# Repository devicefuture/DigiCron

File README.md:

# DigiCron
Software and hardware for the DigiCron smartwatch.

Want to try out the DigiCron's firmware in your browser? Just visit the [DigiCron Simulator](https://digicron.devicefuture.org/simulator)!

## Getting the code
You must clone this repo like this:

```bash
git clone --recurse-submodules https://github.com/devicefuture/digicron
```

`--recurse-submodules` must be used because this repo contains Git submodules which are used as libraries for the firmware and simulator.

## Building
Before building the firmware for the first time, you will need to install the development dependencies:

```bash
./build.sh --install-dev
```

To build the firmware and upload it to the target device over USB, run:

```bash
./build.sh --upload
```

You can also check for compilation errors without uploading by removing the `--upload` flag.

To build the firmware and the simulator, run:

```bash
./build.sh --sim
```

Then to run the simulator locally, you need to start a web server in this directory. You can run the following to start the web server at [localhost:8000](http://localhost:8000):

```bash
python3 -m http.server
```

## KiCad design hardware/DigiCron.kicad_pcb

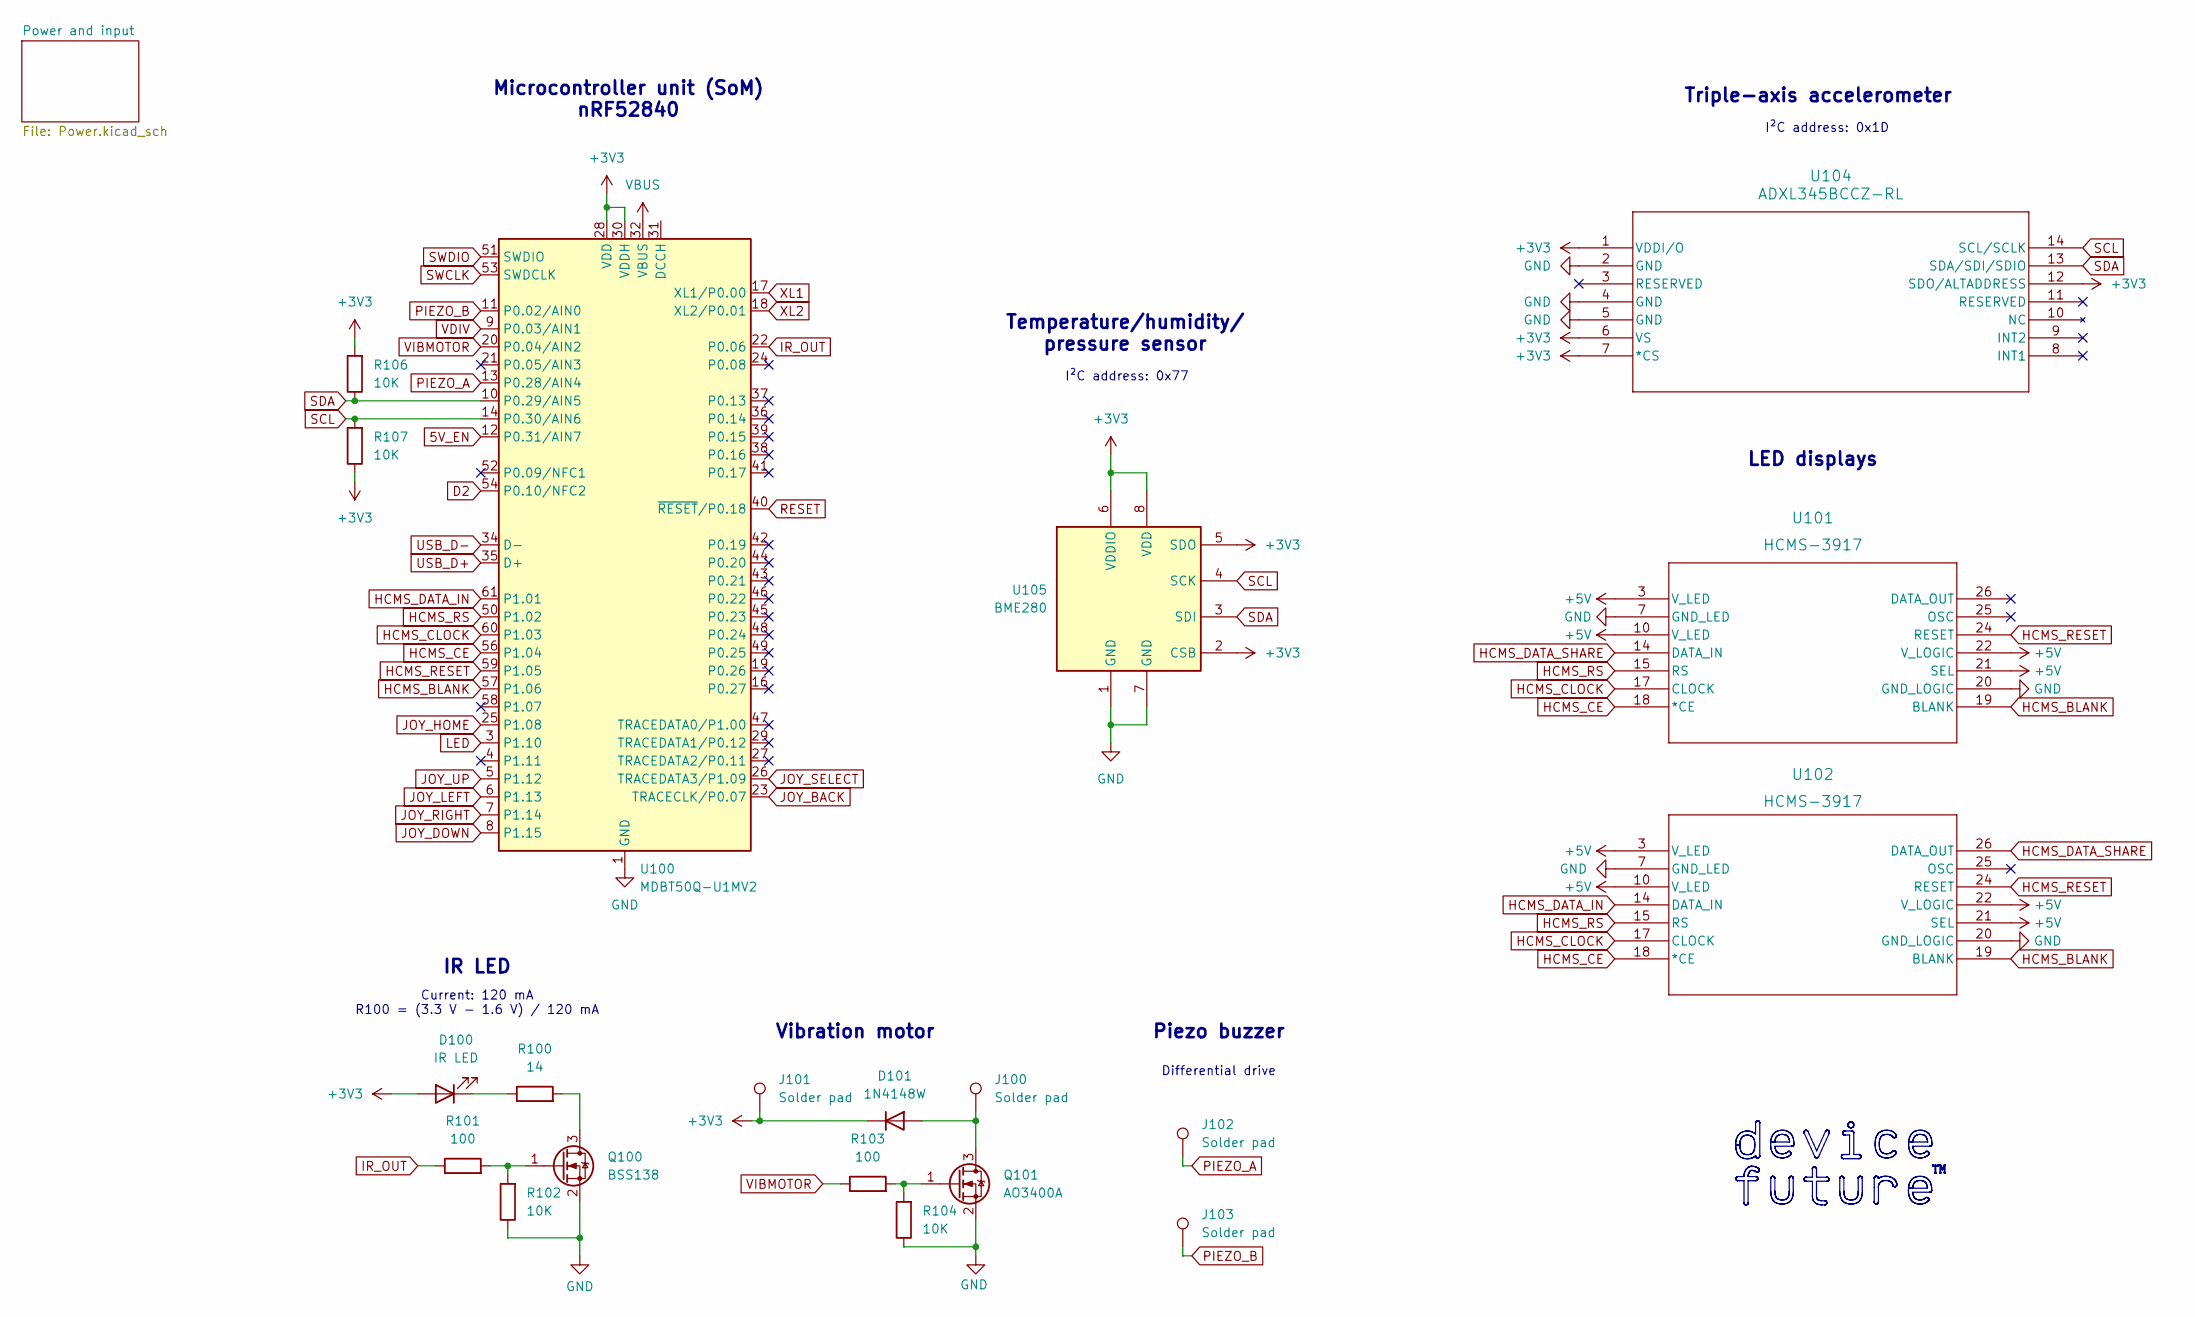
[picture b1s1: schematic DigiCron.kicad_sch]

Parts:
D100: IR LED; LED_D5.0mm_Horizontal_O1.27mm_Z3.0mm_IRBlack
D101: 1N4148W; D_SOD-123
J100, J101, J102, J103: Solder pad; SolderWirePad_1x01_SMD_1x2mm
Q100: BSS138; SOT-23
Q101: AO3400A; SOT-23
R100: 14; R_0402_1005Metric_Pad0.72x0.64mm_HandSolder
R101, R103: 100; R_0402_1005Metric_Pad0.72x0.64mm_HandSolder
R102, R104, R106, R107: 10K; R_0402_1005Metric_Pad0.72x0.64mm_HandSolder
U100: MDBT50Q-U1MV2; Raytac_MDBT50Q
U101, U102: HCMS-3917; DIP26_HCMS-290X-B_BRA
U104: ADXL345BCCZ-RL; LGA_CC-14-1_ADI
U105: BME280; Bosch_LGA-8_2.5x2.5mm_P0.65mm_ClockwisePinNumbering

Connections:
5V_EN: U100.12 (P0.31/AIN7); also elsewhere on the board
+3V3: D100.2 (A), D101.1 (K), J101.1, R106.2, R107.1, U100.28 (VDD), U100.30 (VDDH), U104.1 (VDDI/O), U104.6 (VS), U104.7 (*CS), U104.12 (SDO/ALTADDRESS), U105.2 (CSB), U105.5 (SDO), U105.6 (VDDIO), U105.8 (VDD); also elsewhere on the board
+5V: U101.3 (V_LED), U101.10 (V_LED), U101.21 (SEL), U101.22 (V_LOGIC), U102.3 (V_LED), U102.10 (V_LED), U102.21 (SEL), U102.22 (V_LOGIC); also elsewhere on the board
D2: U100.54 (P0.10/NFC2)
GND: Q100.2 (S), Q101.2 (S), R102.1, R104.1, U100.1 (GND), U100.2 (GND), U100.15 (GND), U100.33 (GND), U100.55 (GND), U101.7 (GND_LED), U101.20 (GND_LOGIC), U102.7 (GND_LED), U102.20 (GND_LOGIC), U104.2 (GND), U104.4 (GND), U104.5 (GND), U105.1 (GND), U105.7 (GND); also elsewhere on the board
HCMS_BLANK: U100.57 (P1.06), U101.19 (BLANK), U102.19 (BLANK)
HCMS_CE: U100.56 (P1.04), U101.18 (*CE), U102.18 (*CE)
HCMS_CLOCK: U100.60 (P1.03), U101.17 (CLOCK), U102.17 (CLOCK)
HCMS_DATA_IN: U100.61 (P1.01), U102.14 (DATA_IN)
HCMS_DATA_SHARE: U101.14 (DATA_IN), U102.26 (DATA_OUT)
HCMS_RESET: U100.59 (P1.05), U101.24 (RESET), U102.24 (RESET)
HCMS_RS: U100.50 (P1.02), U101.15 (RS), U102.15 (RS)
IR_OUT: R101.1, U100.22 (P0.06)
JOY_BACK: U100.23 (TRACECLK/P0.07); also elsewhere on the board
JOY_DOWN: U100.8 (P1.15); also elsewhere on the board
JOY_HOME: U100.25 (P1.08); also elsewhere on the board
JOY_LEFT: U100.6 (P1.13); also elsewhere on the board
JOY_RIGHT: U100.7 (P1.14); also elsewhere on the board
JOY_SELECT: U100.26 (TRACEDATA3/P1.09); also elsewhere on the board
JOY_UP: U100.5 (P1.12); also elsewhere on the board
LED: U100.3 (P1.10)
unnamed: D100.1 (K), R100.1
unnamed: D101.2 (A), J100.1, Q101.3 (D)
unnamed: Q100.3 (D), R100.2
unnamed: Q100.1 (G), R101.2, R102.2
unnamed: Q101.1 (G), R103.2, R104.2
PIEZO_A: J102.1, U100.13 (P0.28/AIN4)
PIEZO_B: J103.1, U100.11 (P0.02/AIN0)
RESET: U100.40 (~RESET/P0.18)
SCL: R107.2, U100.14 (P0.30/AIN6), U104.14 (SCL/SCLK), U105.4 (SCK)
SDA: R106.1, U100.10 (P0.29/AIN5), U104.13 (SDA/SDI/SDIO), U105.3 (SDI)
SWCLK: U100.53 (SWDCLK); also elsewhere on the board
SWDIO: U100.51 (SWDIO); also elsewhere on the board
USB_D+: U100.35 (D+); also elsewhere on the board
USB_D-: U100.34 (D-); also elsewhere on the board
VBUS: U100.32 (VBUS); also elsewhere on the board
VDIV: U100.9 (P0.03/AIN1); also elsewhere on the board
VIBMOTOR: R103.1, U100.20 (P0.04/AIN2)
XL1: U100.17 (XL1/P0.00); also elsewhere on the board
XL2: U100.18 (XL2/P0.01); also elsewhere on the board

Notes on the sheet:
Vibration motor
Temperature/humidity/ pressure sensor
I²C address: 0x77
LED displays
Triple-axis accelerometer
IR LED
Differential drive
I²C address: 0x1D
Piezo buzzer
Current: 120 mA R100 = (3.3 V - 1.6 V) / 120 mA
Microcontroller unit (SoM) nRF52840

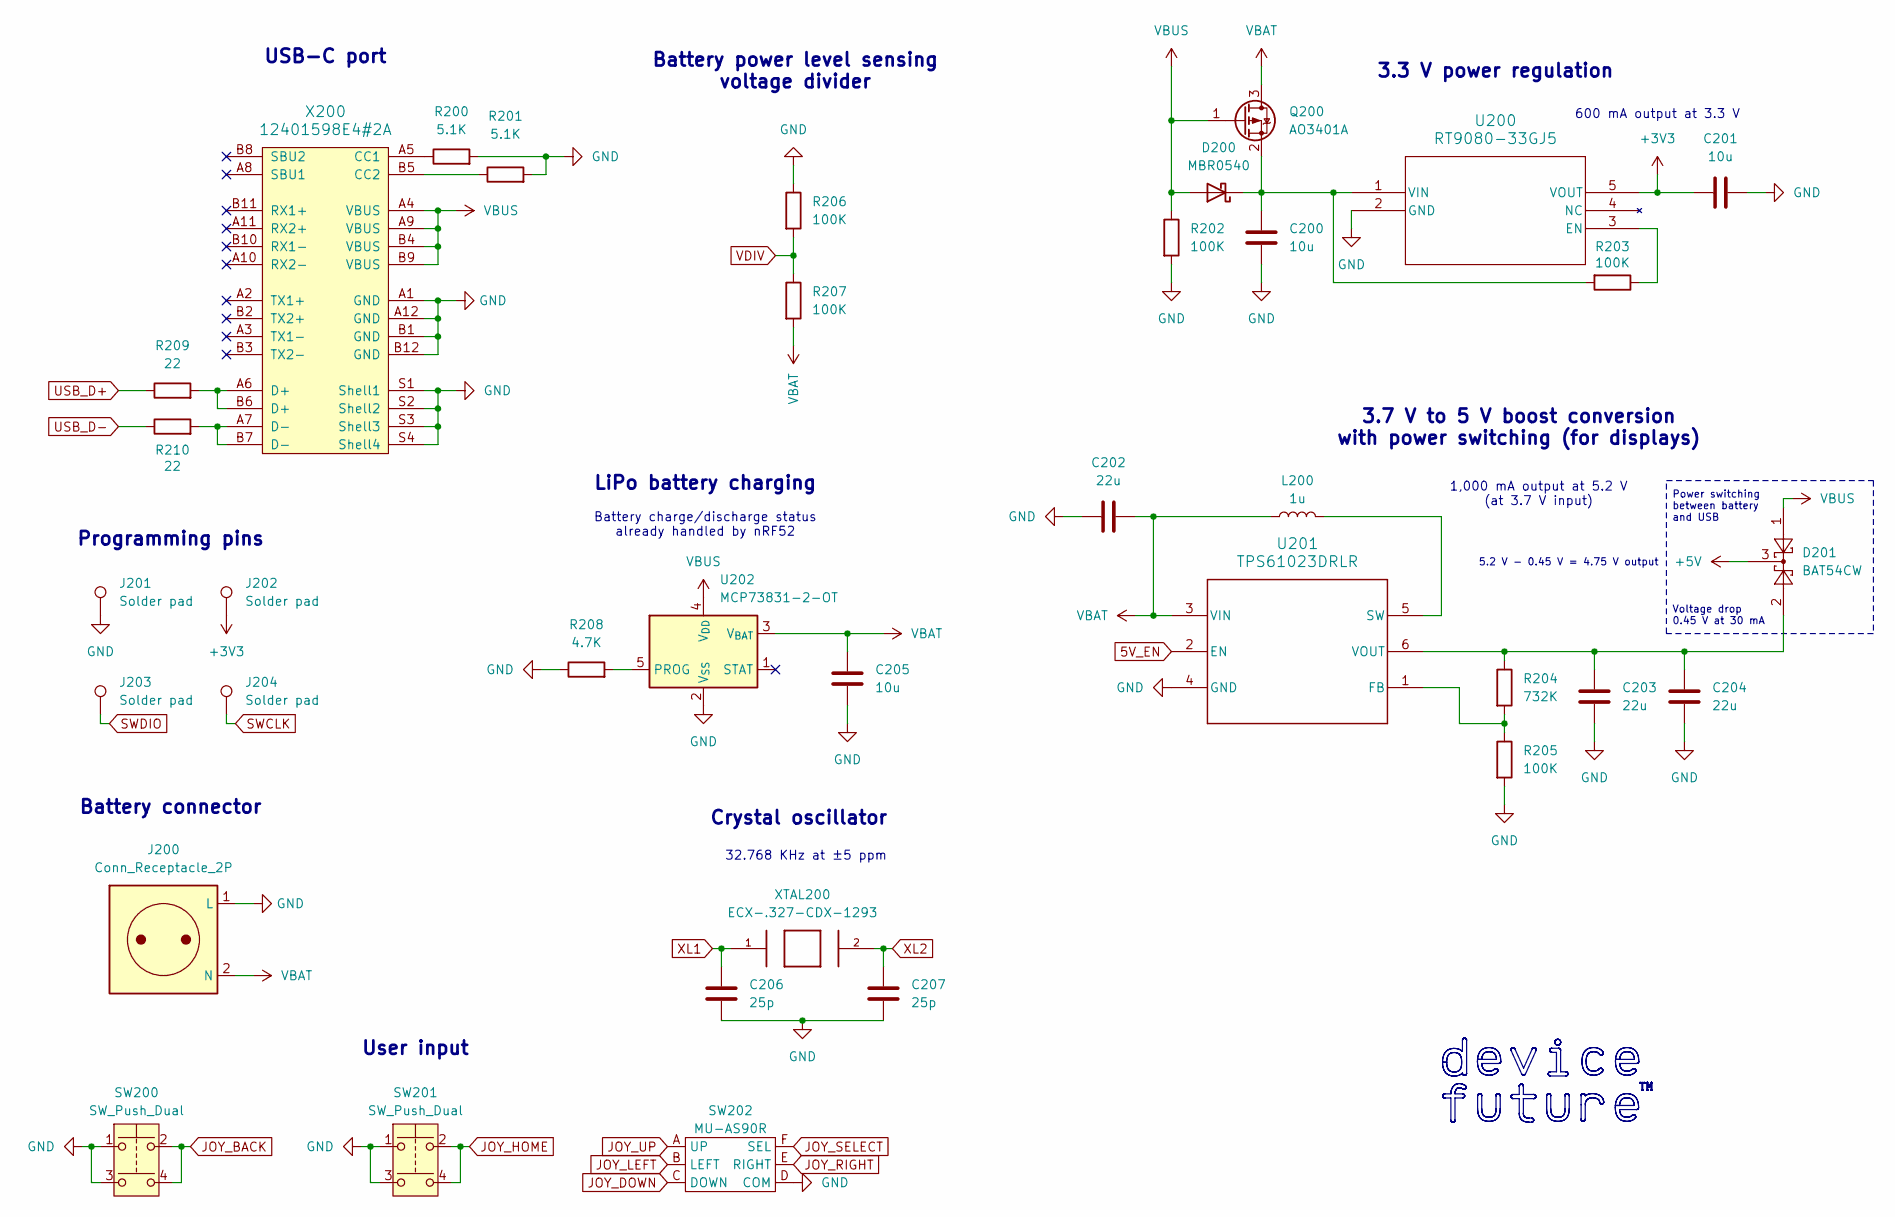
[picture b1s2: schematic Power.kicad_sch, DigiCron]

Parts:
C200, C201, C205: 10u; C_0402_1005Metric_Pad0.74x0.62mm_HandSolder
C202, C203, C204: 22u; C_0402_1005Metric_Pad0.74x0.62mm_HandSolder
C206, C207: 25p; C_0402_1005Metric_Pad0.74x0.62mm_HandSolder
D200: MBR0540; D_SOD-123
D201: BAT54CW; SOT-323_SC-70
J200: Conn_Receptacle_2P; Molex_PicoBlade_53261-0271_1x02-1MP_P1.25mm_Horizontal
J201, J202, J203, J204: Solder pad; TestPoint_Pad_2.0x2.0mm
L200: 1u; L_1008_2520Metric_Pad1.43x2.20mm_HandSolder
Q200: AO3401A; SOT-23-3L_AOS
R200, R201: 5.1K; R_0402_1005Metric_Pad0.72x0.64mm_HandSolder
R202, R203, R205, R206, R207: 100K; R_0402_1005Metric_Pad0.72x0.64mm_HandSolder
R204: 732K; R_0402_1005Metric_Pad0.72x0.64mm_HandSolder
R208: 4.7K; R_0402_1005Metric_Pad0.72x0.64mm_HandSolder
R209, R210: 22; R_0402_1005Metric_Pad0.72x0.64mm_HandSolder
SW200, SW201: SW_Push_Dual; SW_Push_1P1T_NO_6x6mm_H9.5mm
SW202: MU-AS90R
U200: RT9080-33GJ5; TSOT-23-5_RIT
U201: TPS61023DRLR; DRL0006A
U202: MCP73831-2-OT; SOT-23-5
X200: 12401598E4#2A
XTAL200: ECX-.327-CDX-1293; XTAL_ECS-.327-12.5-34RR-TR

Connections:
5V_EN: U201.2 (EN); also elsewhere on the board
+3V3: C201.1, J202.1, U200.5 (VOUT); also elsewhere on the board
+5V: D201.3; also elsewhere on the board
GND: C200.2, C201.2, C202.1, C203.2, C204.2, C205.2, C206.2, C207.2, J200.1 (L), J201.1, R200.2, R201.2, R202.2, R205.2, R206.1, R208.1, SW200.1, SW200.3, SW201.1, SW201.3, SW202.D (COM), U200.2 (GND), U201.4 (GND), U202.2 (V_{SS}), X200.A1 (GND), X200.A12 (GND), X200.B1 (GND), X200.B12 (GND), X200.S1 (Shell1), X200.S2 (Shell2), X200.S3 (Shell3), X200.S4 (Shell4); also elsewhere on the board
JOY_BACK: SW200.2, SW200.4; also elsewhere on the board
JOY_DOWN: SW202.C (DOWN); also elsewhere on the board
JOY_HOME: SW201.2, SW201.4; also elsewhere on the board
JOY_LEFT: SW202.B (LEFT); also elsewhere on the board
JOY_RIGHT: SW202.E (RIGHT); also elsewhere on the board
JOY_SELECT: SW202.F (SEL); also elsewhere on the board
JOY_UP: SW202.A (UP); also elsewhere on the board
unnamed: C200.1, D200.1 (K), Q200.2 (S), R203.2, U200.1 (VIN)
unnamed: R209.2, X200.A6 (D+), X200.B6 (D+)
unnamed: R210.2, X200.A7 (D-), X200.B7 (D-)
unnamed: R203.1, U200.3 (EN)
unnamed: R204.2, R205.1, U201.1 (FB)
unnamed: L200.2, U201.5 (SW)
unnamed: C203.1, C204.1, D201.2, R204.1, U201.6 (VOUT)
unnamed: R208.2, U202.5 (PROG)
unnamed: R200.1, X200.A5 (CC1)
unnamed: R201.1, X200.B5 (CC2)
SWCLK: J204.1; also elsewhere on the board
SWDIO: J203.1; also elsewhere on the board
USB_D+: R209.1; also elsewhere on the board
USB_D-: R210.1; also elsewhere on the board
VBAT: C202.2, C205.1, J200.2 (N), L200.1, Q200.3 (D), R207.2, U201.3 (VIN), U202.3 (V_{BAT})
VBUS: D200.2 (A), D201.1, Q200.1 (G), R202.1, U202.4 (V_{DD}), X200.A4 (VBUS), X200.A9 (VBUS), X200.B4 (VBUS), X200.B9 (VBUS); also elsewhere on the board
VDIV: R206.2, R207.1; also elsewhere on the board
XL1: C206.1, XTAL200.1; also elsewhere on the board
XL2: C207.1, XTAL200.2; also elsewhere on the board

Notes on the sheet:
Battery charge/discharge status already handled by nRF52
Programming pins
Crystal oscillator
600 mA output at 3.3 V
3.7 V to 5 V boost conversion with power switching (for displays)
32.768 KHz at ±5 ppm
1,000 mA output at 5.2 V (at 3.7 V input)
Power switching between battery and USB
Battery power level sensing voltage divider
Battery connector
LiPo battery charging
User input
5.2 V - 0.45 V = 4.75 V output
USB-C port
Voltage drop 0.45 V at 30 mA
3.3 V power regulation

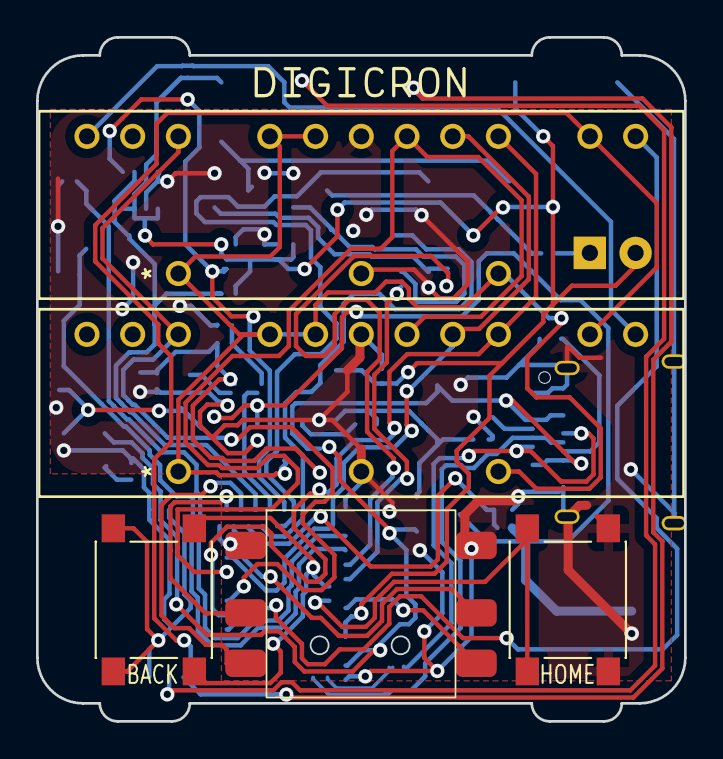
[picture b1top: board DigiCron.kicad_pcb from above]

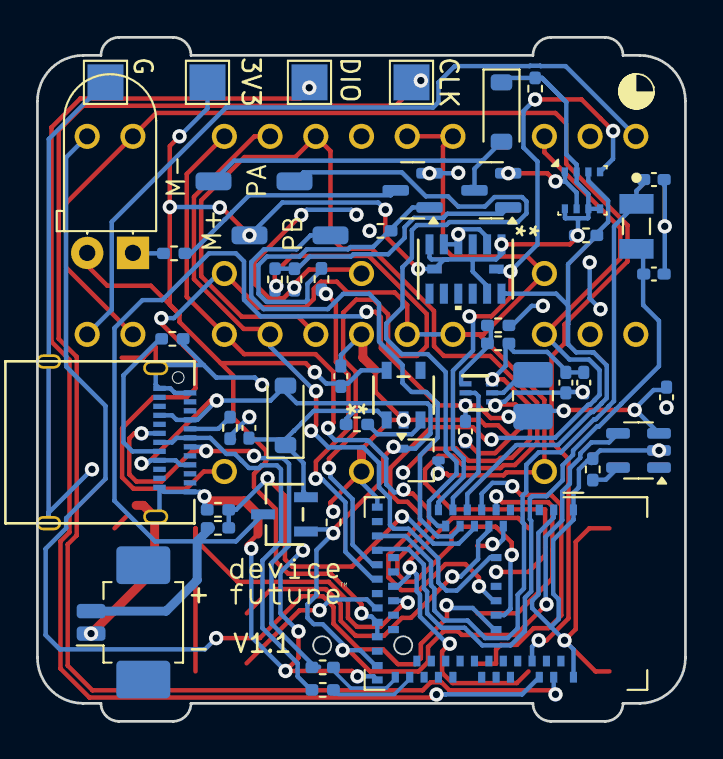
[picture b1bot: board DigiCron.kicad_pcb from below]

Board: 2 copper layers, 36.0 x 38.0 mm, 56 parts (51 on the bottom side), 48 nets.

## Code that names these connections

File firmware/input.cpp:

#ifndef DC_SIMULATOR
    #include <Arduino.h>
#else
    #include <emscripten.h>
    #include <emscripten/bind.h>
#endif

#include "input.h"

#ifndef DC_SIMULATOR

#define BTN_BACK_PIN 6
#define BTN_HOME_PIN 5
#define JOY_UP_PIN 10
#define JOY_DOWN_PIN 12
#define JOY_LEFT_PIN 9
#define JOY_RIGHT_PIN 11
#define JOY_SELECT_PIN 13

void input::init() {
    pinMode(BTN_BACK_PIN, INPUT_PULLUP);
    pinMode(BTN_HOME_PIN, INPUT_PULLUP);
    pinMode(JOY_UP_PIN, INPUT_PULLUP);
    pinMode(JOY_DOWN_PIN, INPUT_PULLUP);
    pinMode(JOY_LEFT_PIN, INPUT_PULLUP);
    pinMode(JOY_RIGHT_PIN, INPUT_PULLUP);
    pinMode(JOY_SELECT_PIN, INPUT_PULLUP);
}

input::Button input::getButtonStatus() {
    if (digitalRead(BTN_BACK_PIN) == LOW) return Button::BACK;
    if (digitalRead(BTN_HOME_PIN) == LOW) return Button::HOME;
    if (digitalRead(JOY_UP_PIN) == LOW) return Button::UP;
    if (digitalRead(JOY_DOWN_PIN) == LOW) return Button::DOWN;
    if (digitalRead(JOY_LEFT_PIN) == LOW) return Button::LEFT;
    if (digitalRead(JOY_RIGHT_PIN) == LOW) return Button::RIGHT;
    if (digitalRead(JOY_SELECT_PIN) == LOW) return Button::SELECT;

    return Button::NONE;
}

#else

input::Button currentButton = input::Button::NONE;

void input::init() {}

input::Button input::getButtonStatus() {
    return currentButton;
}

void setButtonStatus(uint32_t button) {
    currentButton = (input::Button)button;
}

EMSCRIPTEN_BINDINGS(dc_input) {
    emscripten::function("input_setButtonStatus", setButtonStatus);
}

#endif

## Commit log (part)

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2024-09-06 Add basic demo with working display
2024-09-07 Swap out display library for one with a licence
2024-09-08 Get buttons and joystick working
2024-09-10 Implement date and time library
2024-09-10 Add time zone support to time class
2024-09-10 Add battery level and charge/discharge reporting
2024-09-11 Output battery voltage for testing
2024-09-11 Use a more accurate clock by using RTC
2024-09-12 Remove old library from Git submodules
2024-09-12 Add basic simulator
2024-09-13 Add WIP display rendering abstraction
2024-09-14 Add string and icon printing for UI
2024-09-14 Add input abstraction
2024-09-14 Add screen input events
2024-09-15 Reimplement display demo as `ui::Screen`
2024-09-15 Make a few changes to get simulation working again
2024-09-15 Add input buttons to simulator
2024-09-15 Add styling to simulator
2024-09-15 Refactor simulator to move styling and script to new files
2024-09-15 Add more details to readme
2024-09-15 Create CNAME
2024-09-17 Add text scrolling to UI screens
2024-09-17 Add UI menu class and list data type
2024-09-18 Add screen stack and refactor screens to be in own modules
2024-09-19 Add licence
2024-09-20 Add apps menu and contextual menu screens
2024-09-22 Add popup screen type
2024-09-23 Add basic hardware schematic
2024-09-24 Use HCMS BLANK pin to prevent screen glitching
2024-09-25 Add start of WASM runtime integration
2024-09-26 Get WASM execution working
2024-09-28 Refactor API code into own file
2024-09-29 Allow stepping processes including WASM procs
2024-09-29 Remove debug log
2024-09-29 Fix running scheduler cycle on real hardware
2024-12-04 Add start of code generator for WASM API
2024-12-04 Add API code generator as part of main build script
2024-12-04 Generate WASM imports for app lib
2024-12-04 Get basic class instantiation working through API
2024-12-05 Get app lib working with test API
2024-12-06 Allow processes to be passed as first arg to API class constructor
2024-12-07 Get launching screens from apps working
2024-12-07 Get strings working in API
2024-12-07 Add `String` data type for API usage
2024-12-08 Split off shared API functionality into own common area
2024-12-09 Allow reading `__heap_base` in app code
2024-12-09 Access builtin memory size in app as a test
2024-12-09 Implement `malloc`, `free` and `calloc`
2024-12-09 Implement `realloc` function for apps
2024-12-10 Implement instance storage in apps ready for callback functionality
2024-12-11 Implement callable methods on app side
2024-12-11 Add some sensor ICs to schematic
2024-12-12 Replace BMP280 with BME280 and add IR LED and JST connector
2024-12-13 Make minor stylistic syntax change
2024-12-27 Add deletion of app's stored instances when process is stopped (WIP)
2024-12-27 Finish impl of app stored instance deletion upon process stop
2024-12-28 Ensure that WASM memory is freed after process stopped
2024-12-29 Allow functions outside of classes in API
2024-12-30 Allow inheritance in API
2024-12-31 Add syncing `EarthTime` in apps via API
2025-01-01 Implement popups in API
2025-01-02 Refactor menu event handling to prepare for API integration
2025-01-02 Remove unnecessary overrides from API
2025-01-03 Implement menus in API
2025-01-03 Fix string impl to get menus demo working
2025-01-03 Optimise app compilation for size
2025-01-04 Add console module to handle app logs
2025-01-04 Finish adding logging API
2025-01-06 Make a few changes to app build script to fix Clang issue
2025-01-07 Add more BLE service info
2025-01-08 Remove original API used for testing purposes only
2025-01-08 Move test app into dir structure to contain multiple system apps
2025-01-09 Update heap debug code to use new `console::log` API
2025-01-09 Overload `print` to support multiple types and add `pad` method for formatting numbers on display
2025-01-10 Add note about apps being built during main build script
2025-01-11 Improve app launching after returning to home
2025-01-13 Add small note about uploading firmware to device
2025-01-14 Remove button testing code from home screen
2025-01-14 Remove debug console log
2025-01-14 Rebuild firmware for simulator
2025-01-19 Fix including `digicron.h` with multiple source files
2025-01-23 Ensure that deps required to build apps are installed in main build script
2025-01-24 Add app management/registry
2025-01-25 Use view-model approach for counter app
2025-01-26 Add to list of ideas for Counter app
2025-02-06 Add options menu to Counter app
2025-02-08 Impl reset option for Counter app and add confirmation menu
2025-02-08 Fix popup transition
2025-02-09 Add menu option to Counter app to create new counters
2025-02-09 Add start of text input UI and allow returning strings from API
2025-02-10 Add basic UI for text input
2025-02-10 Allow typing letters in text input
2025-02-11 Debounce button input
2025-02-11 Improve basic text editing
2025-02-11 Add menu to confirm text input
2025-02-11 Fix returning bool values from API
2025-02-12 Replace displays with 5V versions (due to supply availability) and add power management ICs
2025-02-12 Remove KiCad backup files
2025-02-12 Change clearance to pass DRC for 0603 components
2025-02-13 Add shift functionality and more characters to text input
2025-02-13 Modify 5V boost converter to use VBAT instead of 3V3 for input and add power switching circuit
2025-02-14 Implement text input scrolling
2025-02-15 Remove help text from menu items as it's too distracting
2025-02-21 Add functionality for creating new counters in counters app
2025-03-05 Fix returning to home screen from main menu when an app is open
2025-03-06 Allow changing between numeric bases in Counter app
2025-03-07 Implement numeric inputs
2025-03-08 Fix a few issues to get working on real hardware
2025-03-08 Fix some compiler warnings when compiling apps
2025-03-09 Don't ask for text input confirmation if value is unchanged
2025-03-10 Tick off todo item for Counter app
2025-03-10 Implement deletion of counters in Counter app
2025-03-11 Capitalise filename of ideas file to differentiate it from other files
2025-03-12 Implement filesystem module for simulator
2025-03-13 Add deletion confirmation menu to Counter app
2025-03-14 Add FS API calls and allow API calls to return `char*`, enums and pointers to other classes
2025-03-14 Comment out FS API declarations for now to allow for compilation on real hardware
2025-03-15 Remove unused API call
2025-03-16 Implement filesystem functionality for real hardware
2025-03-17 Enable API calls for filesystem on real hardware
2025-03-18 Reimpl FS for real hardware to get init working
2025-03-18 Get file reading and writing working on real hardware
2025-03-19 Implement FS directory functions for simulator
2025-03-20 Remove FS function from API that was intended for internal use only
2025-03-20 Add pads for wiring vibration motor and piezo buzzer
2025-03-21 Add note about compiling without uploading from readme
2025-03-22 Reposition USB port on board
2025-03-22 Use custom icon for shift key in text inputs
2025-03-22 Fix shorter text input menu items
2025-03-24 Add start of config helper class
2025-03-25 Fix memory issues when merging free blocks
2025-03-25 Fix INI parser in config and add config reading demo to test app
2025-03-25 Fix memory issue when parsing INI files
2025-03-25 Comment out debug code again
2025-03-25 Fix a few minor memory leaks
2025-03-25 Rebuild after memory leak fixes
2025-03-25 Fix memory issues relating to block merging
2025-03-27 Test FS directory listing and fix a few listing issues
2025-03-28 Add non-string getter and setter methods to config class
2025-03-29 Add `fs::ensureParentDirectories` function to API
2025-03-30 Add todo to remove 2025's leap second
2025-03-30 Implement CRUD integration with FS for Counter app
2025-03-30 Fix a few filesystem problems and other issues
2025-03-31 Redesign number utils and ensure counters are added in sequential order in Counter app
2025-03-31 Update to-do list for Counter app
2025-04-01 Allow reassignment of buttons in Counter app
2025-04-01 Make some improvements to memory usage for Counter app
2025-04-01 Fix a few small issues with console logs and API
2025-04-03 Modify readme to ensure simulator links to actual page
2025-05-11 Get compilation of wasmu working
2025-05-14 Fix issues to get code running
2025-05-14 Update wasmu
2025-05-17 Add integration with catto
2025-05-17 Implement population of system files at startup
2025-05-17 Make atto `print` command show text on screen
2025-05-18 Get count loop working in atto
2025-05-18 Free catto context when stopping atto app
2025-05-20 Improve power sources for IR LED, vibration motor and piezo buzzer
2025-05-20 Reduce power consumption of IR LED
2025-05-21 Add voltage divider and replace boost converter
2025-05-21 Add battery charging circuit
2025-05-22 Make a few minor adjustments and add headings to schematic
2025-05-27 Increase display brightness for use with HCMS-29xx
2025-05-27 Add buttons to PCB layout
2025-05-27 Add joystick to PCB
2025-05-27 Make a few tweaks to joystick on PCB
2025-05-28 Add programming pins to PCB
2025-05-28 Add crystal oscillator and hide designators from PCB
2025-05-30 Implement menus in atto apps
2025-06-02 Fix flash corruption when overwriting system files
2025-06-02 Use menu index variable to set initial item shown
2025-06-02 Rebuild simulator
2025-06-05 Fix freeing memory when replacing app process
2025-06-05 Rebuild simulator WASM
2025-06-28 Make minor clarification to readme
2025-07-06 Update catto and implement a few fixes
2025-07-07 Add basic Counter app
2025-07-09 Update catto to use new field accessor syntax
2025-07-09 Update catto to fix memory issues
2025-07-09 Improve speed of process stepping
2025-07-10 Change `menu` behaviour to accept extra argument to set initial index
2025-07-10 Add `input` command to atto
2025-07-11 Add confirmation menu (`yesno` and `noyes`) commands to atto
2025-07-13 Implement `intinput` and input options in atto
2025-07-20 Perform PCB routing (WIP)
2025-07-20 Clean up some VBAT traces
2025-07-20 Finish routing of PCB
2025-07-24 Check over PCB design and re-add LTR390
2025-07-25 Add branding to back side of PCB
2025-07-26 Add mounting tabs to edges of PCB
2025-07-26 Make minor alterations to not use custom font on PCB
2025-07-26 Update PCB to use 0402 resistor/capacitor packages
2025-08-06 Update catto to include cattoX support
2025-08-07 Test using attoX in Test app
2025-08-08 Implement file `open` and `close` commands in atto
2025-08-09 Implement `read` and `write` commands in atto
2025-08-09 Update catto to fix CSV issue
2025-08-09 Defer saving counters in Counter app
2025-08-11 Upgrade filesystem to fix issues when overwriting files
2025-08-11 Move app items onto main menu
2025-08-12 Make minor update to description
2025-08-13 Add lap and split timing to stopwatch
2025-08-14 Implement `delay` command in atto
2025-08-15 Refactor Stopwatch app to use individual rendering functions
2025-08-16 Make minor tweaks to behaviour of Stopwatch app
2025-08-18 Make minor clarification to simulator link text
2025-08-24 Implement loading indicator in menus for when launching apps
2025-08-25 Allow apps to be force stopped by holding back button
2025-08-25 Fix a few minor memory leaks affecting Counter app
2025-08-26 Remove outdated information about system apps from readme
2025-08-27 Update atto to include OOM safety
2025-08-27 Update catto again
2025-08-28 Add HTML BOM for PCB
2025-08-30 Make a few changes to footprint selection and resistor/capacitor values
2025-10-11 Add minor clarification to readme
2025-10-17 Change wording in readme for link to visit simulator
2025-12-04 Fix symbols used in todo comment for text input code
2026-01-01 Reroute MCU pins to avoid vias inside pads
2026-01-01 Remove LTR-390 to make assembly easier
2026-01-01 Fix pin routing for battery power level sensing
2026-01-01 Make minor routing tweak
2026-01-02 Fix minor routing error
2026-01-02 Bump version number on PCB and schematics
2026-01-02 Make minor change to layout in schematic
2026-01-05 Make minor clarification in readme
2026-01-08 Add boot animation
2026-01-09 Make minor improvement to boot animation timings
